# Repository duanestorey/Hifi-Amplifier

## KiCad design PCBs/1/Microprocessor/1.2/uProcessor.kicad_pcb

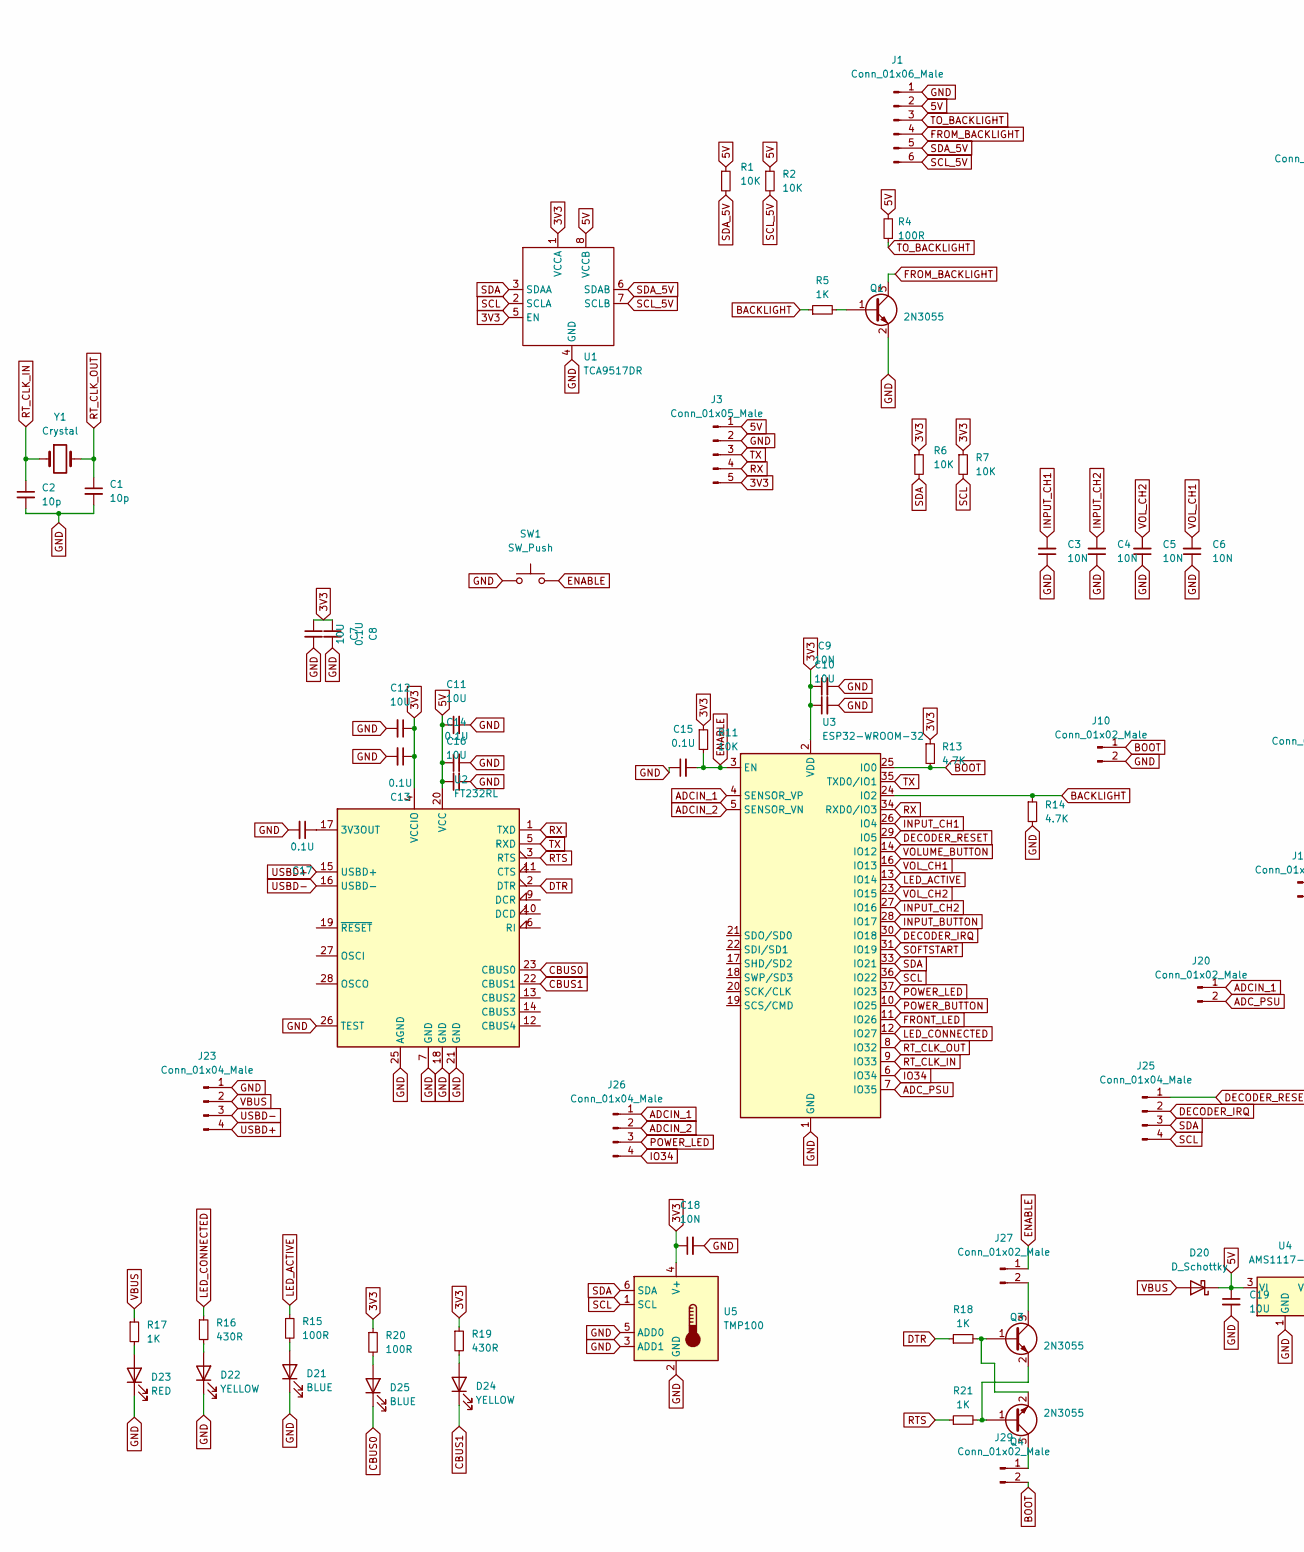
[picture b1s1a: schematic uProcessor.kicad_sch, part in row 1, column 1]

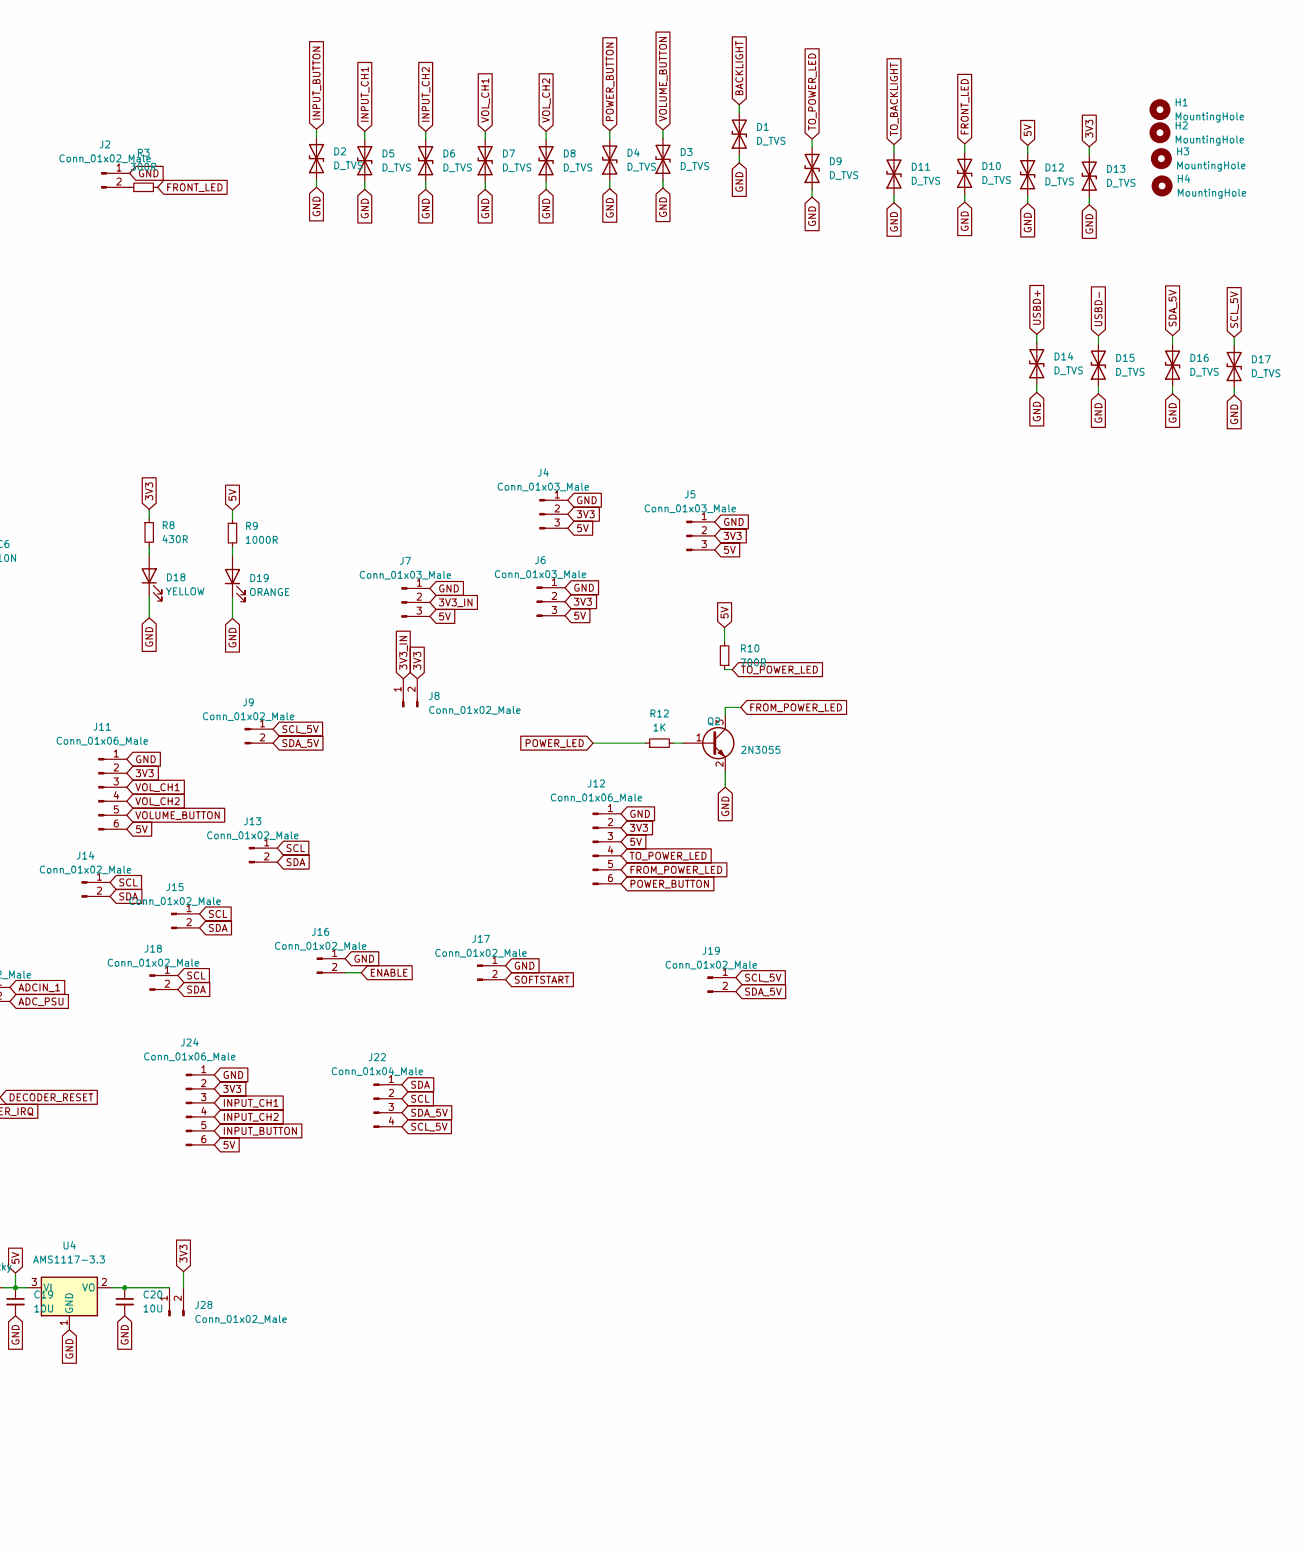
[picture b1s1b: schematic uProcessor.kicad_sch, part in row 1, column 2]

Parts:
C1, C2: 10p; C_0603_1608Metric_Pad1.08x0.95mm_HandSolder
C3, C4, C5, C6: 10N; C_0603_1608Metric_Pad1.08x0.95mm_HandSolder
C7, C10, C11, C12, C16, C19, C20: 10U; C_1206_3216Metric_Pad1.33x1.80mm_HandSolder
C8, C13, C14, C15, C17: 0.1U; C_0805_2012Metric_Pad1.18x1.45mm_HandSolder
C9, C18: 10N; C_0805_2012Metric_Pad1.18x1.45mm_HandSolder
D1, D2, D3, D4, D5, D6, D7, D8, D9, D10, D11, D12, D13, D14, D15, D16, D17: D_TVS; D_SOD-523
D18: YELLOW; LED_0805_2012Metric_Pad1.15x1.40mm_HandSolder; LCSC NCD0603R1
D19: ORANGE; LED_0805_2012Metric_Pad1.15x1.40mm_HandSolder; LCSC XL-1608UBC-04
D20: D_Schottky; D_SMA_Handsoldering
D21, D25: BLUE; LED_0805_2012Metric_Pad1.15x1.40mm_HandSolder; LCSC XL-1608UBC-04
D22, D24: YELLOW; LED_0805_2012Metric_Pad1.15x1.40mm_HandSolder; LCSC XL-1608UBC-04
D23: RED; LED_0805_2012Metric_Pad1.15x1.40mm_HandSolder; LCSC XL-1608UBC-04
H1, H2, H3, H4: MountingHole; MountingHole_3.2mm_M3
J1, J11, J12, J24: Conn_01x06_Male; JST_PH_B6B-PH-K_1x06_P2.00mm_Vertical
J2, J9, J13, J14, J15, J16, J17, J18, J19, J20: Conn_01x02_Male; JST_PH_B2B-PH-K_1x02_P2.00mm_Vertical
J3: Conn_01x05_Male; PinSocket_1x05_P2.54mm_Vertical
J4, J6: Conn_01x03_Male; PinHeader_1x03_P2.54mm_Vertical
J5, J7: Conn_01x03_Male; JST_PH_B3B-PH-K_1x03_P2.00mm_Vertical
J8, J10, J27, J28, J29: Conn_01x02_Male; PinHeader_1x02_P2.54mm_Vertical
J22, J26: Conn_01x04_Male; PinHeader_1x04_P2.54mm_Vertical
J23, J25: Conn_01x04_Male; JST_PH_B4B-PH-K_1x04_P2.00mm_Vertical
Q1, Q2, Q3, Q4: 2N3055; TSOT-23
R1, R2, R6, R7, R11: 10K; R_0603_1608Metric_Pad0.98x0.95mm_HandSolder
R3: 300R; R_0603_1608Metric_Pad0.98x0.95mm_HandSolder
R4, R15, R20: 100R; R_0603_1608Metric_Pad0.98x0.95mm_HandSolder
R5, R12, R17, R18, R21: 1K; R_0603_1608Metric_Pad0.98x0.95mm_HandSolder
R8, R16, R19: 430R; R_0603_1608Metric_Pad0.98x0.95mm_HandSolder
R9: 1000R; R_0603_1608Metric_Pad0.98x0.95mm_HandSolder
R10: 700R; R_0603_1608Metric_Pad0.98x0.95mm_HandSolder
R13, R14: 4.7K; R_0603_1608Metric_Pad0.98x0.95mm_HandSolder
SW1: SW_Push; Button Aliexpress 4x4
U1: TCA9517DR; SOIC-8_3.9x4.9mm_P1.27mm
U2: FT232RL; SSOP-28_5.3x10.2mm_P0.65mm
U3: ESP32-WROOM-32; ESP32-WROOM-32UE
U4: AMS1117-3.3; SOT-223-3_TabPin2
U5: TMP100; SOT-23-6
Y1: Crystal; Crystal_SMD_EuroQuartz_EQ161-2Pin_3.2x1.5mm_HandSoldering

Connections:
3V3: C7.1, C8.1, C9.1, C10.1, C12.1, C13.1, C18.1, D13.2 (A2), J3.5, J4.2, J5.2, J6.2, J8.2, J11.2, J12.2, J24.2, J28.2, R6.1, R7.1, R8.1, R11.1, R13.1, R19.1, R20.1, U1.1 (VCCA), U1.5 (EN), U2.4 (VCCIO), U3.2 (VDD), U5.4 (V+)
3V3_IN: J7.2, J8.1
5V: C11.1, C14.1, C16.1, C19.1, D12.2 (A2), D20.1 (K), J1.2, J3.1, J4.3, J5.3, J6.3, J7.3, J11.6, J12.3, J24.6, R1.1, R2.1, R4.2, R9.1, R10.2, U1.8 (VCCB), U2.20 (VCC), U4.3 (VI)
ADCIN_1: J20.1, J26.1, U3.4 (SENSOR_VP)
ADCIN_2: J26.2, U3.5 (SENSOR_VN)
ADC_PSU: J20.2, U3.7 (IO35)
BACKLIGHT: D1.2 (A2), R5.1, R14.1, U3.24 (IO2)
BOOT: J10.1, J29.2, R13.2, U3.25 (IO0)
CBUS0: D25.1 (K), U2.23 (CBUS0)
CBUS1: D24.1 (K), U2.22 (CBUS1)
DECODER_IRQ: J25.2, U3.30 (IO18)
DECODER_RESET: J25.1, U3.29 (IO5)
ENABLE: C15.2, J16.2, J27.1, R11.2, SW1.2, U3.3 (EN)
FROM_BACKLIGHT: J1.4, Q1.3 (C)
FROM_POWER_LED: J12.5, Q2.3 (C)
FRONT_LED: D10.2 (A2), R3.2, U3.11 (IO26)
GND: C1.2, C2.2, C3.1, C4.1, C5.1, C6.1, C7.2, C8.2, C9.2, C10.2, C11.2, C12.2, C13.2, C14.2, C15.1, C16.2, C17.2, C18.2, C19.2, C20.2, D1.1 (A1), D2.1 (A1), D3.1 (A1), D4.1 (A1), D5.1 (A1), D6.1 (A1), D7.1 (A1), D8.1 (A1), D9.1 (A1), D10.1 (A1), D11.1 (A1), D12.1 (A1), D13.1 (A1), D14.1 (A1), D15.1 (A1), D16.1 (A1), D17.1 (A1), D18.1 (K), D19.1 (K), D21.1 (K), D22.1 (K), D23.1 (K), J1.1, J2.1, J3.2, J4.1, J5.1, J6.1, J7.1, J10.2, J11.1, J12.1, J16.1, J17.1, J23.1, J24.1, Q1.2 (E), Q2.2 (E), R14.2, SW1.1, U1.4 (GND), U2.7 (GND), U2.18 (GND), U2.21 (GND), U2.25 (AGND), U2.26 (TEST), U3.1 (GND), U3.15 (GND), U3.38 (GND), U3.39 (GND), U4.1 (GND), U5.2 (GND), U5.3 (ADD1), U5.5 (ADD0); also elsewhere on the board
INPUT_BUTTON: D2.2 (A2), J24.5, U3.28 (IO17)
INPUT_CH1: C3.2, D5.2 (A2), J24.3, U3.26 (IO4)
INPUT_CH2: C4.2, D6.2 (A2), J24.4, U3.27 (IO16)
IO34: J26.4, U3.6 (IO34)
LED_ACTIVE: R15.1, U3.13 (IO14)
LED_CONNECTED: R16.1, U3.12 (IO27)
unnamed: D18.2 (A), R8.2
unnamed: D19.2 (A), R9.2
unnamed: D21.2 (A), R15.2
unnamed: D22.2 (A), R16.2
unnamed: D23.2 (A), R17.2
unnamed: D24.2 (A), R19.2
unnamed: D25.2 (A), R20.2
unnamed: J2.2, R3.1
unnamed: J27.2, Q3.3 (C)
unnamed: C20.1, J28.1, U4.2 (VO)
unnamed: J29.1, Q4.3 (C)
unnamed: Q1.1 (B), R5.2
unnamed: Q2.1 (B), R12.2
unnamed: C17.1, U2.17 (3V3OUT)
POWER_BUTTON: D4.2 (A2), J12.6, U3.10 (IO25)
POWER_LED: J26.3, R12.1, U3.37 (IO23)
RT_CLK_IN: C2.1, U3.9 (IO33), Y1.1
RT_CLK_OUT: C1.1, U3.8 (IO32), Y1.2
RX: J3.4, U2.1 (TXD), U3.34 (RXD0/IO3)
SCL: J13.1, J14.1, J15.1, J18.1, J22.2, J25.4, R7.2, U1.2 (SCLA), U3.36 (IO22), U5.1 (SCL)
SCL_5V: D17.2 (A2), J1.6, J9.1, J19.1, J22.4, R2.2, U1.7 (SCLB)
SDA: J13.2, J14.2, J15.2, J18.2, J22.1, J25.3, R6.2, U1.3 (SDAA), U3.33 (IO21), U5.6 (SDA)
SDA_5V: D16.2 (A2), J1.5, J9.2, J19.2, J22.3, R1.2, U1.6 (SDAB)
SOFTSTART: J17.2, U3.31 (IO19); also elsewhere on the board
TO_BACKLIGHT: D11.2 (A2), J1.3, R4.1
TO_POWER_LED: D9.2 (A2), J12.4, R10.1
TX: J3.3, U2.5 (RXD), U3.35 (TXD0/IO1)
USBD+: D14.2 (A2), J23.4, U2.15 (USBD+)
USBD-: D15.2 (A2), J23.3, U2.16 (USBD-)
VBUS: D20.2 (A), J23.2, R17.1
VOLUME_BUTTON: D3.2 (A2), J11.5, U3.14 (IO12)
VOL_CH1: C6.2, D7.2 (A2), J11.3, U3.16 (IO13)
VOL_CH2: C5.2, D8.2 (A2), J11.4, U3.23 (IO15)

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
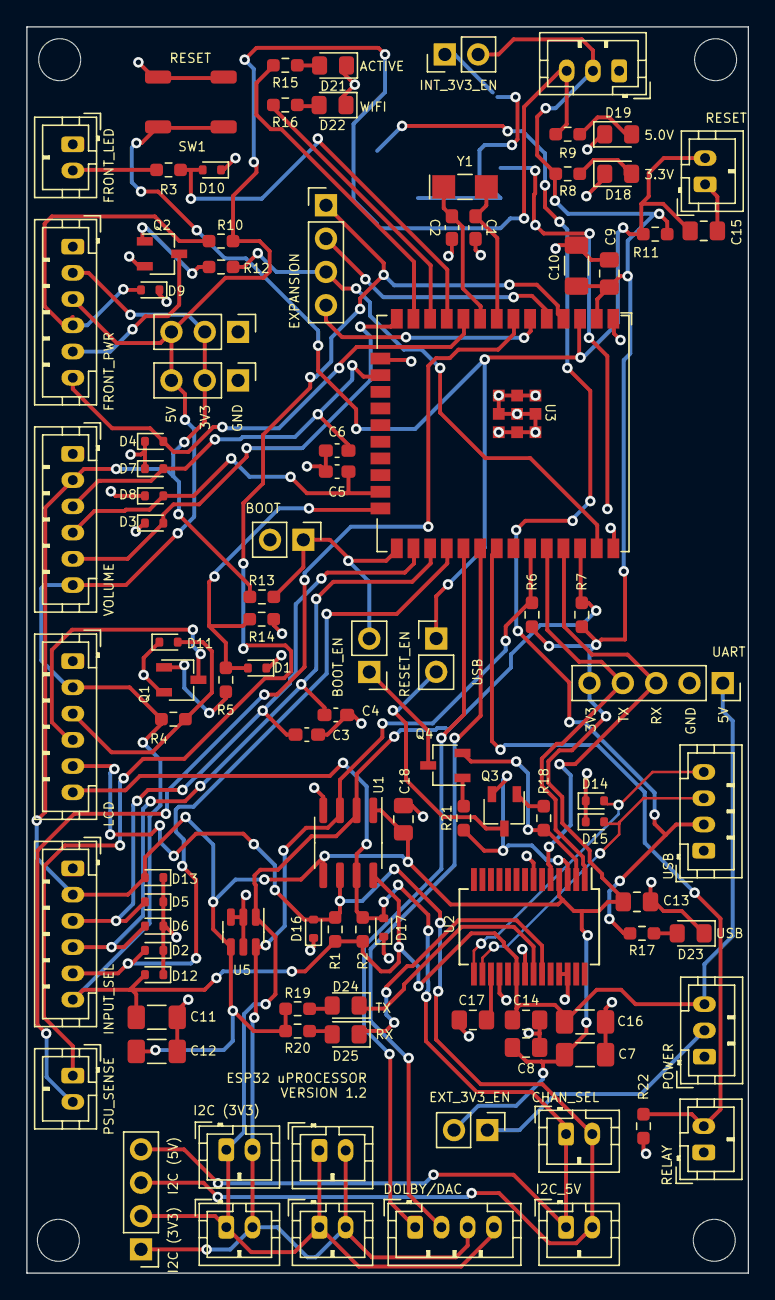
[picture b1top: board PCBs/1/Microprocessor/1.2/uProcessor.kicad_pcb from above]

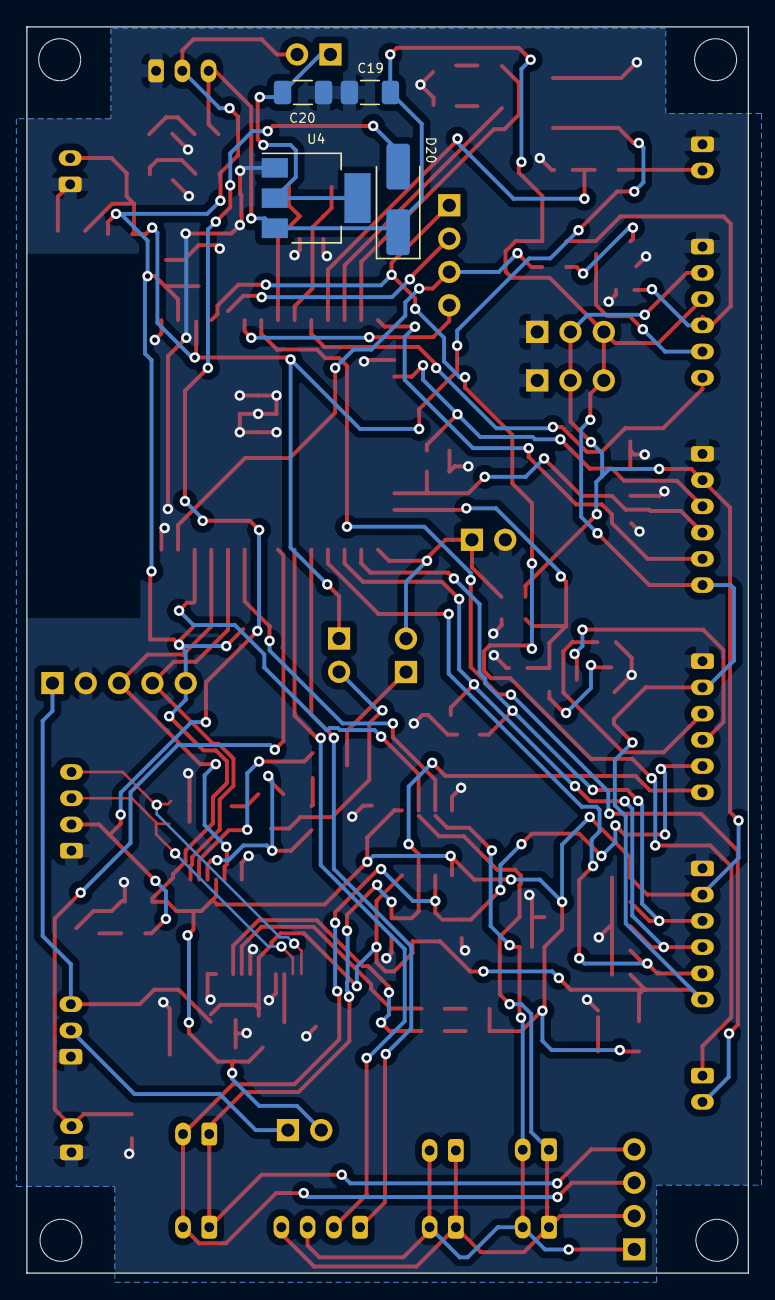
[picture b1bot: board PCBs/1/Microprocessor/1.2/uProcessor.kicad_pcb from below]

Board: 2 copper layers, 55.0 x 95.0 mm, 110 parts (4 on the bottom side), 60 nets.

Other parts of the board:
R22: 4K7; R_0603_1608Metric_Pad0.98x0.95mm_HandSolder

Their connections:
GND: R22.1; also elsewhere on the board
SOFTSTART: R22.2; also elsewhere on the board

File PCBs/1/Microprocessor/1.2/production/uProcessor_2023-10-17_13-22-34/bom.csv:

Designator,Footprint,Quantity,Value,LCSC Part #
"C1, C2",0603,2,10p,
"C10, C11, C12, C16, C19, C20, C7",1206,7,10U,
"C13, C14, C15, C17, C8",0805,5,0.1U,
"C18, C9",0805,2,10N,
"C3, C4, C5, C6",0603,4,10N,
"D1, D10, D11, D12, D13, D14, D15, D16, D17, D2, D3, D4, D5, D6, D7, D8, D9",D_SOD-523,17,D_TVS,
D18,0805,1,YELLOW,NCD0603R1
D19,0805,1,ORANGE,XL-1608UBC-04
D20,D_SMA_Handsoldering,1,D_Schottky,
"D21, D25",0805,2,BLUE,XL-1608UBC-04
"D22, D24",0805,2,YELLOW,XL-1608UBC-04
D23,0805,1,RED,XL-1608UBC-04
"H1, H2, H3, H4",MountingHole_3.2mm_M3,4,MountingHole,
"J1, J11, J12, J24",JST_PH_B6B-PH-K_1x06_P2.00mm_Vertical,4,Conn_01x06_Male,
"J10, J27, J28, J29, J8",PinHeader_1x02_P2.54mm_Vertical,5,Conn_01x02_Male,
"J13, J14, J15, J16, J17, J18, J19, J2, J20, J9",JST_PH_B2B-PH-K_1x02_P2.00mm_Vertical,10,Conn_01x02_Male,
"J22, J26",PinHeader_1x04_P2.54mm_Vertical,2,Conn_01x04_Male,
"J23, J25",JST_PH_B4B-PH-K_1x04_P2.00mm_Vertical,2,Conn_01x04_Male,
J3,PinSocket_1x05_P2.54mm_Vertical,1,Conn_01x05_Male,
"J4, J6",PinHeader_1x03_P2.54mm_Vertical,2,Conn_01x03_Male,
"J5, J7",JST_PH_B3B-PH-K_1x03_P2.00mm_Vertical,2,Conn_01x03_Male,
"Q1, Q2, Q3, Q4",TSOT-23,4,2N3055,
"R1, R11, R2, R6, R7",0603,5,10K,
R10,0603,1,700R,
"R12, R17, R18, R21, R5",0603,5,1K,
"R13, R14",0603,2,4.7K,
"R15, R20, R4",0603,3,100R,
"R16, R19, R8",0603,3,430R,
R3,0603,1,300R,
R9,0603,1,1000R,
SW1,Button Aliexpress 4x4,1,SW_Push,
U1,SOIC-8_3.9x4.9mm_P1.27mm,1,TCA9517DR,
U2,SSOP-28_5.3x10.2mm_P0.65mm,1,FT232RL,
U3,ESP32-WROOM-32UE,1,ESP32-WROOM-32,
U4,SOT-223-3_TabPin2,1,AMS1117-3.3,
U5,SOT-23-6,1,TMP100,
Y1,Crystal_SMD_EuroQuartz_EQ161-2Pin_3.2x1.5mm_HandSoldering,1,Crystal,

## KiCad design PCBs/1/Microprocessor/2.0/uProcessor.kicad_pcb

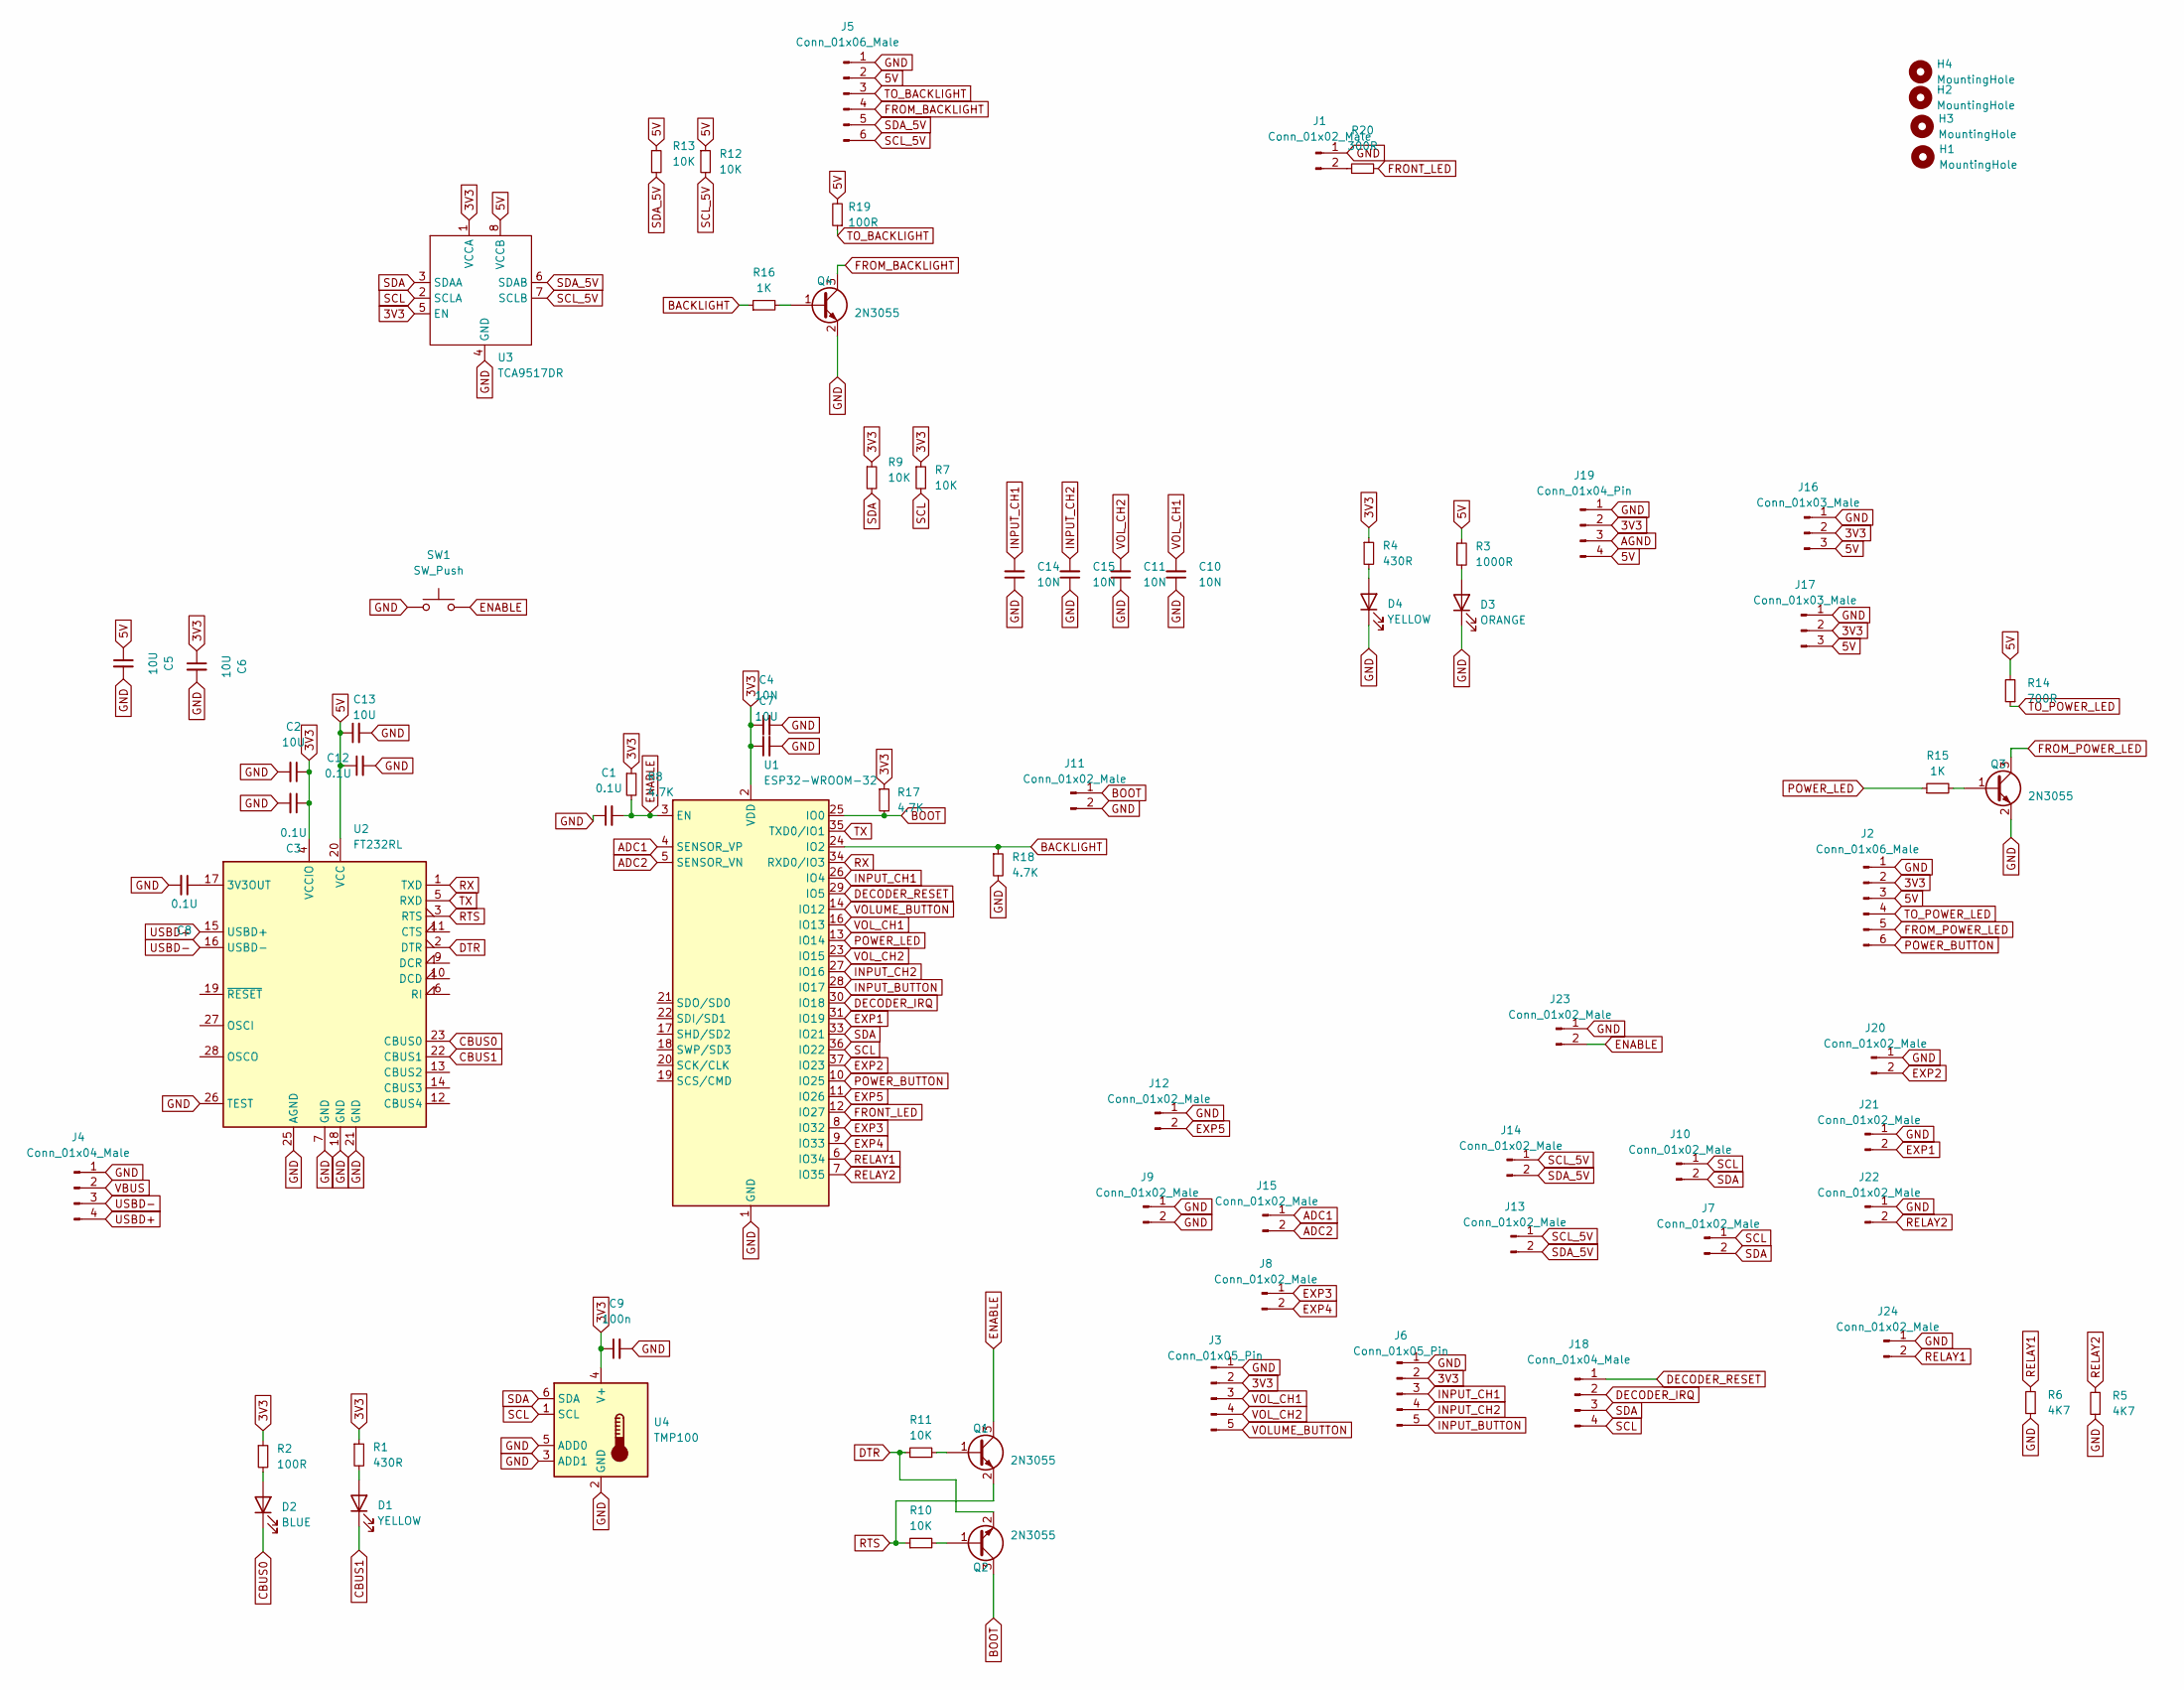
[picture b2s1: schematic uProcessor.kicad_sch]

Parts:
C1, C3, C8, C12: 0.1U; C_0805_2012Metric_Pad1.18x1.45mm_HandSolder
C2, C5, C6, C7, C13: 10U; C_1206_3216Metric_Pad1.33x1.80mm_HandSolder
C4: 10N; C_0805_2012Metric_Pad1.18x1.45mm_HandSolder
C9: 100n; C_0805_2012Metric_Pad1.18x1.45mm_HandSolder
C10, C11, C14, C15: 10N; C_0603_1608Metric_Pad1.08x0.95mm_HandSolder
D1: YELLOW; LED_0805_2012Metric_Pad1.15x1.40mm_HandSolder; LCSC XL-1608UBC-04
D2: BLUE; LED_0805_2012Metric_Pad1.15x1.40mm_HandSolder; LCSC XL-1608UBC-04
D3: ORANGE; LED_0805_2012Metric_Pad1.15x1.40mm_HandSolder; LCSC XL-1608UBC-04
D4: YELLOW; LED_0805_2012Metric_Pad1.15x1.40mm_HandSolder; LCSC NCD0603R1
H1, H2, H3, H4: MountingHole; MountingHole_3.2mm_M3
J1, J7, J10, J13, J14, J20, J21, J22, J23, J24: Conn_01x02_Male; JST_PH_B2B-PH-K_1x02_P2.00mm_Vertical
J2, J5: Conn_01x06_Male; JST_PH_B6B-PH-K_1x06_P2.00mm_Vertical
J3, J6: Conn_01x05_Pin; JST_PH_B5B-PH-K_1x05_P2.00mm_Vertical
J4, J18: Conn_01x04_Male; JST_PH_B4B-PH-K_1x04_P2.00mm_Vertical
J8, J9, J11, J12, J15: Conn_01x02_Male; PinHeader_1x02_P2.54mm_Vertical
J16, J17: Conn_01x03_Male; PinHeader_1x03_P2.54mm_Vertical
J19: Conn_01x04_Pin; JST_XH_B4B-XH-A_1x04_P2.50mm_Vertical
Q1, Q2, Q3, Q4: 2N3055; TSOT-23
R1, R4: 430R; R_0603_1608Metric_Pad0.98x0.95mm_HandSolder
R2, R19: 100R; R_0603_1608Metric_Pad0.98x0.95mm_HandSolder
R3: 1000R; R_0603_1608Metric_Pad0.98x0.95mm_HandSolder
R5, R6: 4K7; R_0603_1608Metric_Pad0.98x0.95mm_HandSolder
R7, R9, R10, R11, R12, R13: 10K; R_0603_1608Metric_Pad0.98x0.95mm_HandSolder
R8, R17, R18: 4.7K; R_0603_1608Metric_Pad0.98x0.95mm_HandSolder
R14: 700R; R_0603_1608Metric_Pad0.98x0.95mm_HandSolder
R15, R16: 1K; R_0603_1608Metric_Pad0.98x0.95mm_HandSolder
R20: 300R; R_0603_1608Metric_Pad0.98x0.95mm_HandSolder
SW1: SW_Push; Button Aliexpress 4x4
U1: ESP32-WROOM-32; ESP32-WROOM-32UE
U2: FT232RL; SSOP-28_5.3x10.2mm_P0.65mm
U3: TCA9517DR; SOIC-8_3.9x4.9mm_P1.27mm
U4: TMP100; SOT-23-6

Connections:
3V3: C2.1, C3.1, C4.1, C6.1, C7.1, C9.1, J2.2, J3.2, J6.2, J16.2, J17.2, J19.2, R1.1, R2.1, R4.1, R7.1, R8.1, R9.1, R17.1, U1.2 (VDD), U2.4 (VCCIO), U3.1 (VCCA), U3.5 (EN), U4.4 (V+)
5V: C5.1, C12.1, C13.1, J2.3, J5.2, J16.3, J17.3, J19.4, R3.1, R12.1, R13.1, R14.2, R19.2, U2.20 (VCC), U3.8 (VCCB)
ADC1: J15.1, U1.4 (SENSOR_VP)
ADC2: J15.2, U1.5 (SENSOR_VN)
AGND: J19.3
BACKLIGHT: R16.1, R18.1, U1.24 (IO2)
BOOT: J11.1, Q2.3 (C), R17.2, U1.25 (IO0)
CBUS0: D2.1 (K), U2.23 (CBUS0)
CBUS1: D1.1 (K), U2.22 (CBUS1)
DECODER_IRQ: J18.2, U1.30 (IO18)
DECODER_RESET: J18.1, U1.29 (IO5)
DTR: Q2.2 (E), R11.1, U2.2 (DTR)
ENABLE: C1.2, J23.2, Q1.3 (C), R8.2, SW1.2, U1.3 (EN)
EXP1: J21.2, U1.31 (IO19)
EXP2: J20.2, U1.37 (IO23)
EXP3: J8.1, U1.8 (IO32)
EXP4: J8.2, U1.9 (IO33)
EXP5: J12.2, U1.11 (IO26)
FROM_BACKLIGHT: J5.4, Q4.3 (C)
FROM_POWER_LED: J2.5, Q3.3 (C)
FRONT_LED: R20.2, U1.12 (IO27)
GND: C1.1, C2.2, C3.2, C4.2, C5.2, C6.2, C7.2, C8.2, C9.2, C10.1, C11.1, C12.2, C13.2, C14.1, C15.1, D3.1 (K), D4.1 (K), J1.1, J2.1, J3.1, J4.1, J5.1, J6.1, J9.1, J9.2, J11.2, J12.1, J16.1, J17.1, J19.1, J20.1, J21.1, J22.1, J23.1, J24.1, Q3.2 (E), Q4.2 (E), R5.1, R6.1, R18.2, SW1.1, U1.1 (GND), U1.15 (GND), U1.38 (GND), U1.39 (GND), U2.7 (GND), U2.18 (GND), U2.21 (GND), U2.25 (AGND), U2.26 (TEST), U3.4 (GND), U4.2 (GND), U4.3 (ADD1), U4.5 (ADD0)
INPUT_BUTTON: J6.5, U1.28 (IO17)
INPUT_CH1: C14.2, J6.3, U1.26 (IO4)
INPUT_CH2: C15.2, J6.4, U1.27 (IO16)
unnamed: D1.2 (A), R1.2
unnamed: D2.2 (A), R2.2
unnamed: D3.2 (A), R3.2
unnamed: D4.2 (A), R4.2
unnamed: J1.2, R20.1
unnamed: Q1.1 (B), R11.2
unnamed: Q2.1 (B), R10.2
unnamed: Q3.1 (B), R15.2
unnamed: Q4.1 (B), R16.2
unnamed: C8.1, U2.17 (3V3OUT)
POWER_BUTTON: J2.6, U1.10 (IO25)
POWER_LED: R15.1, U1.13 (IO14)
RELAY1: J24.2, R6.2, U1.6 (IO34)
RELAY2: J22.2, R5.2, U1.7 (IO35)
RTS: Q1.2 (E), R10.1, U2.3 (RTS)
RX: U1.34 (RXD0/IO3), U2.1 (TXD)
SCL: J7.1, J10.1, J18.4, R7.2, U1.36 (IO22), U3.2 (SCLA), U4.1 (SCL)
SCL_5V: J5.6, J13.1, J14.1, R12.2, U3.7 (SCLB)
SDA: J7.2, J10.2, J18.3, R9.2, U1.33 (IO21), U3.3 (SDAA), U4.6 (SDA)
SDA_5V: J5.5, J13.2, J14.2, R13.2, U3.6 (SDAB)
TO_BACKLIGHT: J5.3, R19.1
TO_POWER_LED: J2.4, R14.1
TX: U1.35 (TXD0/IO1), U2.5 (RXD)
USBD+: J4.4, U2.15 (USBD+)
USBD-: J4.3, U2.16 (USBD-)
VBUS: J4.2
VOLUME_BUTTON: J3.5, U1.14 (IO12)
VOL_CH1: C10.2, J3.3, U1.16 (IO13)
VOL_CH2: C11.2, J3.4, U1.23 (IO15)

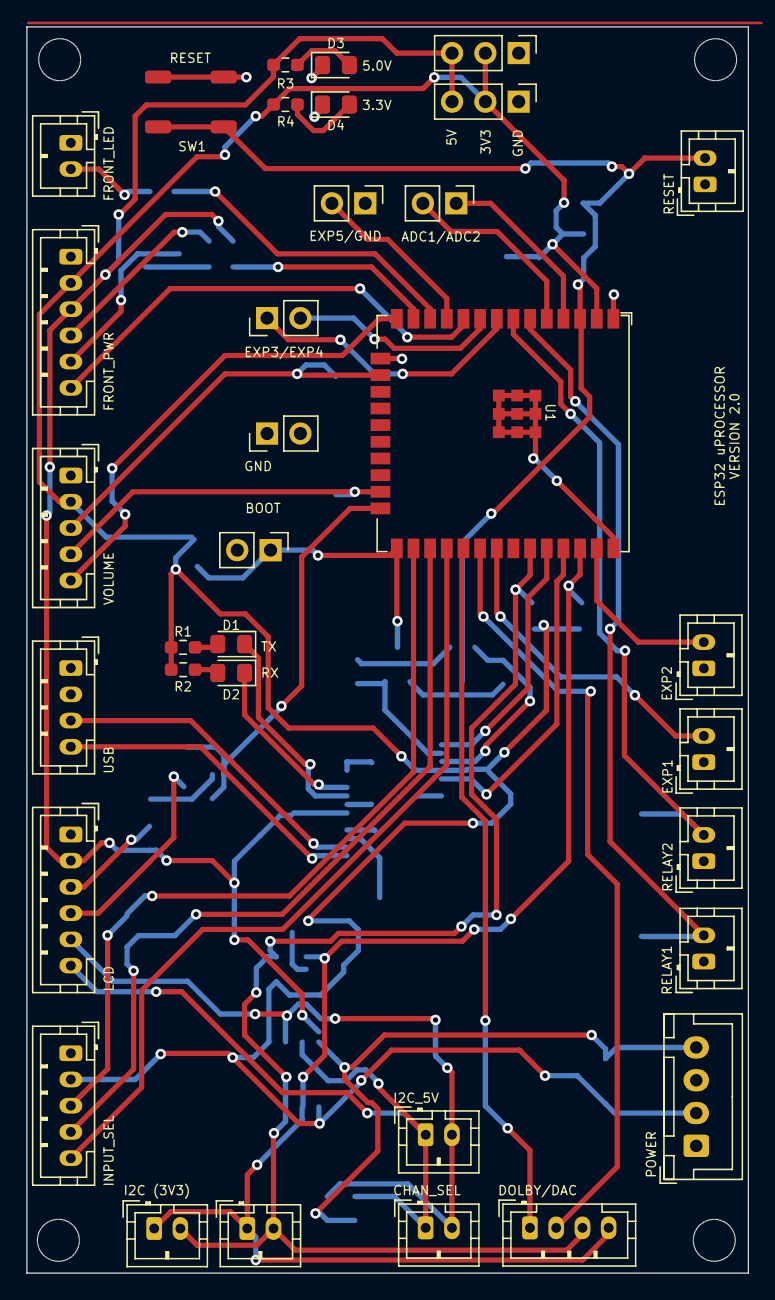
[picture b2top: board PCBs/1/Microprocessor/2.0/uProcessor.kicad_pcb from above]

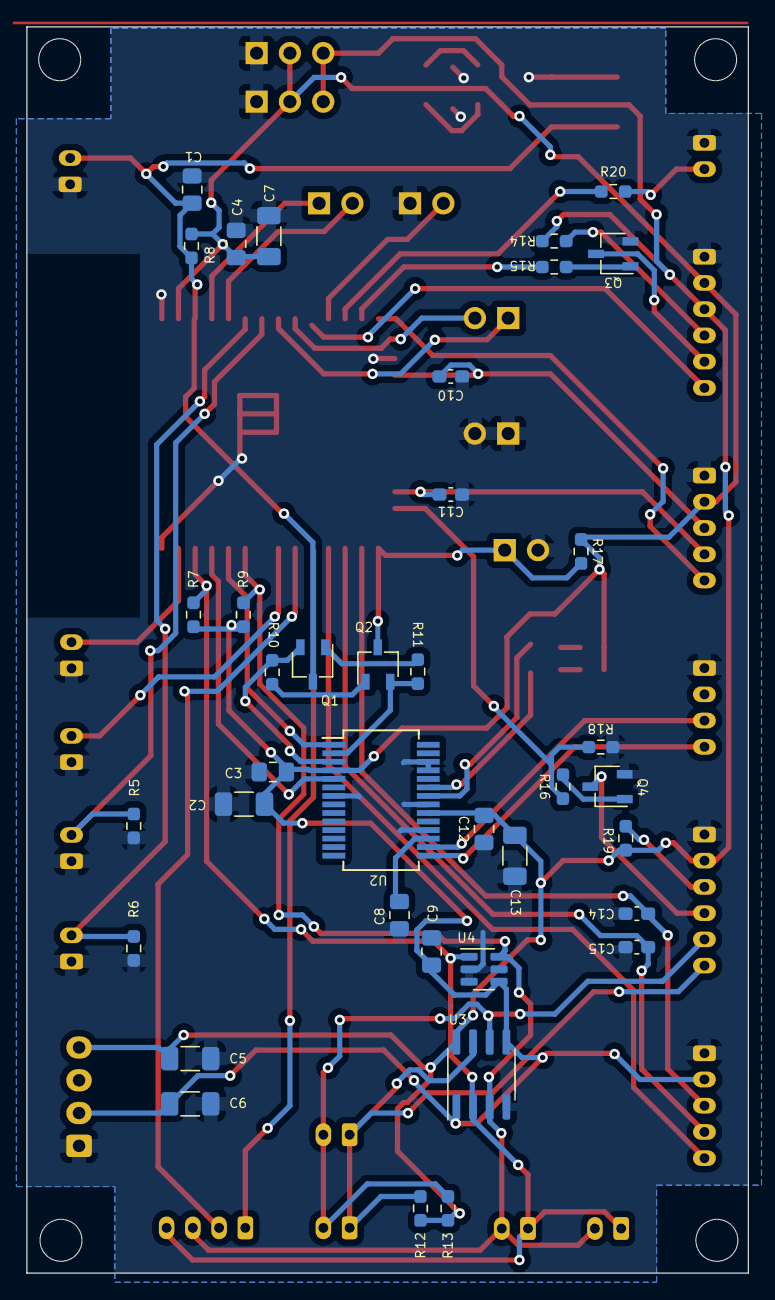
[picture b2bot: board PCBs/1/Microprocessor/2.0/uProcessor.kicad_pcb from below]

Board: 2 copper layers, 55.0 x 95.0 mm, 76 parts (38 on the bottom side), 52 nets.

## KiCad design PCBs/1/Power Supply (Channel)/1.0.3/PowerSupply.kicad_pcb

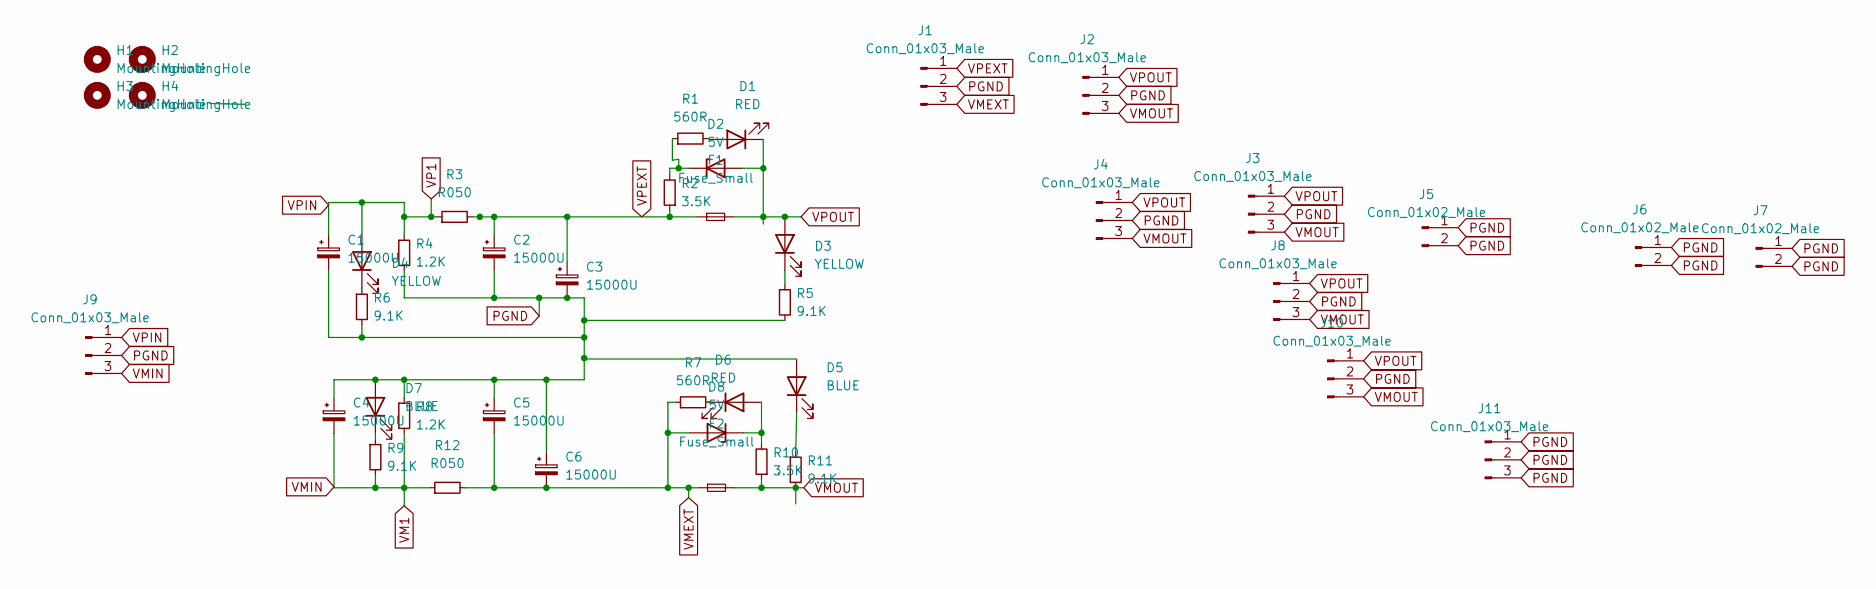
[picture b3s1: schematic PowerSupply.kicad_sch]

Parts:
C1, C2, C3, C4, C5, C6: 15000U; CP_Radial_D30.0mm_P10.00mm_SnapIn
D1, D6: RED; LED_0805_2012Metric_Pad1.15x1.40mm_HandSolder
D2, D8: 5V; D_MELF
D3, D4: YELLOW; LED_0805_2012Metric_Pad1.15x1.40mm_HandSolder
D5, D7: BLUE; LED_0805_2012Metric_Pad1.15x1.40mm_HandSolder
F1, F2: Fuse_Small; 5x20mm AliExpress 250V 6A
H1, H3: MountingHole; MountingHole_3mm
H2, H4: MountingHole; MountingHole_3.2mm_M3
J1, J2, J3, J4, J8, J9, J10: Conn_01x03_Male; JST_VH_B3P-VH_1x03_P3.96mm_Vertical
J5, J6: Conn_01x02_Male; JST_PH_B2B-PH-K_1x02_P2.00mm_Vertical
J7: Conn_01x02_Male; JST_VH_B2P-VH-B_1x02_P3.96mm_Vertical
J11: Conn_01x03_Male; JST_PH_B3B-PH-K_1x03_P2.00mm_Vertical
R1, R7: 560R; R_0805_2012Metric_Pad1.20x1.40mm_HandSolder
R2, R10: 3.5K; R_1206_3216Metric_Pad1.30x1.75mm_HandSolder
R3, R12: R050; R_2512_6332Metric_Pad1.40x3.35mm_HandSolder
R4, R8: 1.2K; R_2512_6332Metric_Pad1.40x3.35mm_HandSolder
R5, R6, R9, R11: 9.1K; R_0805_2012Metric_Pad1.20x1.40mm_HandSolder

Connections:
unnamed: D1.2 (A), R1.2
unnamed: D2.1 (K), R1.1, R2.2
unnamed: D3.1 (K), R5.1
unnamed: D4.1 (K), R6.1
unnamed: D5.1 (K), R11.1
unnamed: D6.1 (K), R7.2
unnamed: D6.2 (A), D8.1 (K), R10.2
unnamed: D7.1 (K), R9.1
PGND: C1.2, C2.2, C3.2, C4.1, C5.1, C6.1, D5.2 (A), D7.2 (A), J1.2, J2.2, J3.2, J4.2, J5.1, J5.2, J6.1, J6.2, J7.1, J7.2, J8.2, J9.2, J10.2, J11.1, J11.2, J11.3, R4.2, R5.2, R6.2, R8.1
VM1: C4.2, J9.3, R8.2, R9.2, R12.1
VMEXT: C5.2, C6.2, D8.2 (A), F2.1, J1.3, R7.1, R12.2
VMOUT: F2.2, J2.3, J3.3, J4.3, J8.3, J10.3, R10.1, R11.2
VP1: C1.1, D4.2 (A), J9.1, R3.1, R4.1
VPEXT: C2.1, C3.1, F1.1, J1.1, R2.1, R3.2
VPOUT: D1.1 (K), D2.2 (A), D3.2 (A), F1.2, J2.1, J3.1, J4.1, J8.1, J10.1
